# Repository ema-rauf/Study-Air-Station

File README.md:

# Study Air Station

A desk air quality monitor. It measures CO2, fine dust, temperature and humidity, shows a live score on a color display, runs a fan when the air gets bad, and sends a Telegram message when it is time to open a window. Everything is logged to a microSD card.

## Why I made it

When I study in a closed room, CO2 climbs past 1500 ppm within an hour and I get tired without knowing why. I wanted a device that shows the number, reacts on its own and keeps a record, so I can see how a room behaves over a day.

## How it works

An ESP32 reads two sensors:

- SCD40 over I2C for CO2, temperature and humidity
- PMS5003 over UART for PM1.0, PM2.5 and PM10

From these it computes a 0 to 100 score and a state (fine, stuffy, alert). The score drives an RGB LED and a bar on the 2.0 inch ST7789 display. The display has three pages, switched with the page button: live values, a 24 hour CO2 graph, and system info.

Layout preview of the three alert states, drawn by the firmware's display code with sample values.

- **Fan.** A 5 V fan is switched by an IRLZ44N. It turns on at 1000 ppm CO2 or 25 ug/m3 PM2.5 and off again 200 ppm and 10 ug/m3 lower, with a 60 second minimum run or rest time so it does not chatter. A long press on the page button forces it on, off or back to auto.
- **Alerts.** At 1500 ppm or 55 ug/m3 the LED blinks red, the buzzer beeps every 30 seconds and a Telegram message is sent immediately. The silence button mutes the buzzer for 10 minutes, then it re-arms by itself. A second message goes out when the air is back to normal.
- **Logging.** One CSV line per minute with a timestamp goes to the microSD card, one file per day. Time comes from NTP, so there is no RTC.
- **Dashboard.** A password protected web page on the local network shows live values, the 24 hour graph, fan and silence controls, the thresholds (editable, kept in flash) and a download link for today's log.

## Hardware

Two layer board, 100 x 80 mm. The ESP32 DevKit plugs into sockets. The SCD40, display, microSD module and PMS5003 connect with short jumper cables to pin headers, so each can sit where it works best in the case. The fan and the 5 V supply use screw terminals. The board takes 5 V on a screw terminal, through a Schottky diode against reverse polarity. Use the ESP32 USB port for programming with the 5 V terminal unplugged.

| Function | ESP32 pin |
| --- | --- |
| SCD40 SDA / SCL | IO21 / IO22 |
| PMS5003 TX to ESP32 / ESP32 to PMS5003 RX | IO16 / IO17 |
| TFT SCK, MOSI | IO33, IO25 (shared with the SD card) |
| TFT CS, DC, RES | IO14, IO27, IO26 |
| SD MISO, CS | IO34, IO32 |
| Fan gate | IO23 |
| Buzzer | IO4 |
| RGB LED R, G, B | IO19, IO18, IO5 |
| Silence button, page button | IO36, IO39 (10k pull-ups on the board) |

## Case

`cad/air_station_case.step` holds a base, a lid and two button caps. The PCB sits on four standoffs on the left. The bay on the right holds the PMS5003 on the floor, the microSD module and the SCD40 standing on their edges in rib slots, and a 25 mm fan on the back wall. The base has a USB opening, a cable opening for the 5 V input, intake slots, an SD card slot in the east wall and air slots for the SCD40. The lid has the display window above the bay and two button holes with printed caps. It takes about 120 g of filament.

## Firmware

`firmware/air_station/air_station.ino`, built with the Arduino IDE.

1. Install the ESP32 board package (board: ESP32 Dev Module).
2. Install the libraries Adafruit GFX Library and Adafruit ST7789 Library.
3. Edit the settings block at the top: WiFi name and password, dashboard password, Telegram bot token and chat id (optional), time zone.
4. Flash. The dashboard stays off until the default dashboard password is changed.

Buttons: silence short press mutes or unmutes. Page short press changes the page, long press cycles the fan mode.

Telegram alerts use HTTPS without certificate checking, so keep the bot token to a bot used only for this. The dashboard uses plain HTTP and basic authentication, so use it on a trusted network only.

## Files

- `hardware/` KiCad project (schematic, PCB, project libraries)
- `firmware/air_station/` Arduino sketch
- `cad/` case, STEP
- `BOM.csv` parts, prices, links
- `images/` renders

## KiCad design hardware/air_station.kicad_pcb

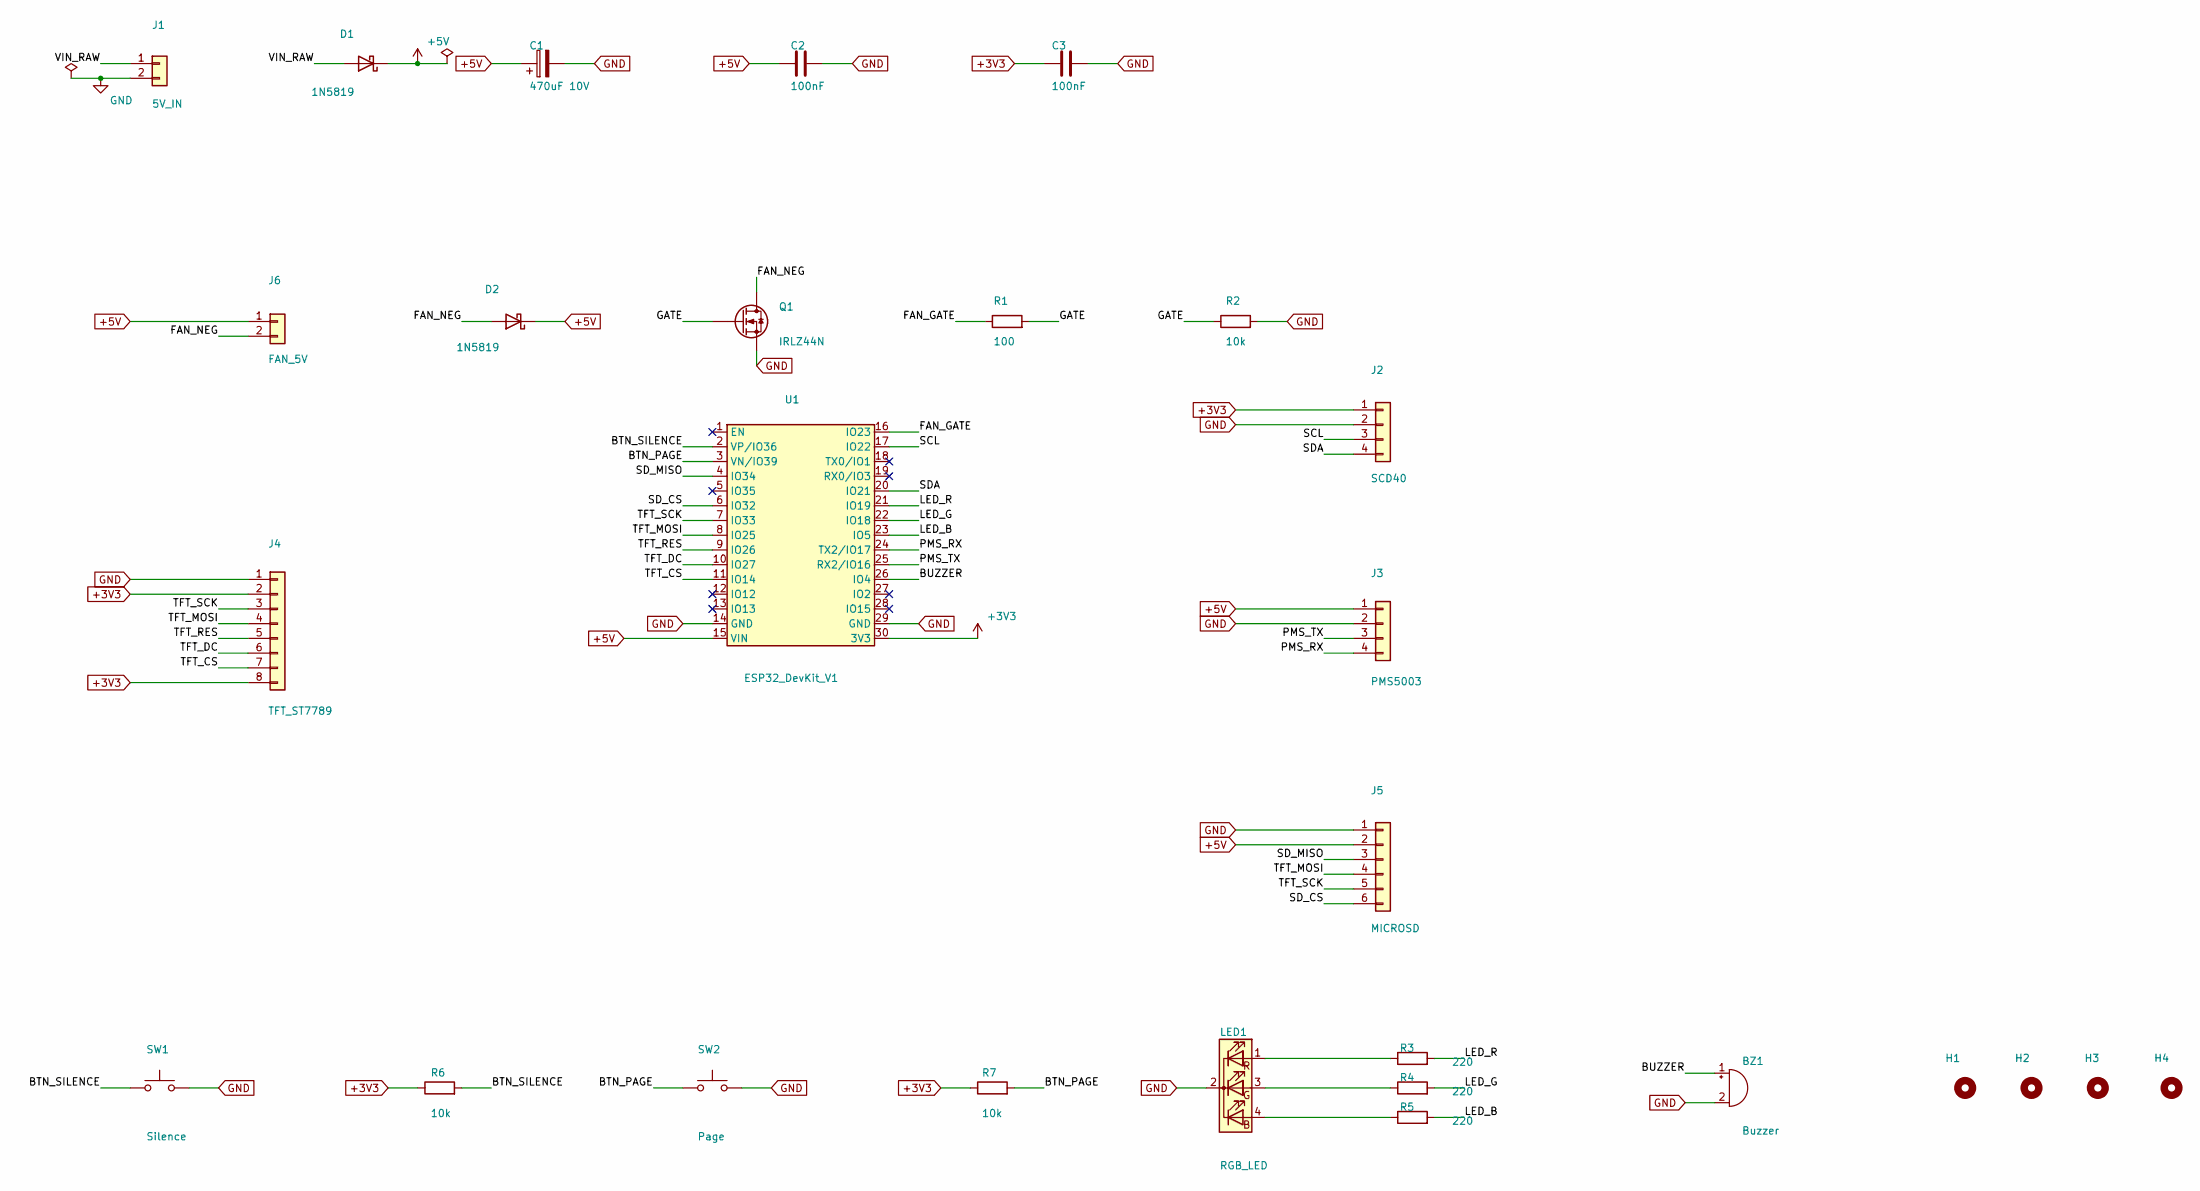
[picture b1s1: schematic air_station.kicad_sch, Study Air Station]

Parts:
BZ1: Buzzer; Buzzer_12x9.5RM7.6
C1: 470uF 10V; CP_Radial_D8.0mm_P3.50mm
C2, C3: 100nF; C_Disc_D5.0mm_W2.5mm_P5.00mm
D1, D2: 1N5819; D_DO-41_SOD81_P10.16mm_Horizontal
H1, H2, H3, H4: MountingHole_3.2mm; MountingHole_3.2mm_M3
J1: 5V_IN; TerminalBlock_Phoenix_MKDS-1,5-2-5.08_1x02_P5.08mm_Horizont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
J2: SCD40; PinHeader_1x04_P2.54mm_Vertical
J3: PMS5003; PinHeader_1x04_P2.54mm_Vertical
J4: TFT_ST7789; PinHeader_1x08_P2.54mm_Vertical
J5: MICROSD; PinHeader_1x06_P2.54mm_Vertical
J6: FAN_5V; TerminalBlock_Phoenix_MKDS-1,5-2-5.08_1x02_P5.08mm_Horizont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
LED1: RGB_LED; LED_D5.0mm-4_RGB_Wide
Q1: IRLZ44N; TO-220-3_Vertical
R1: 100; R_Axial_DIN0204_L3.6mm_D1.6mm_P5.08mm_Horizontal
R2, R6, R7: 10k; R_Axial_DIN0204_L3.6mm_D1.6mm_P5.08mm_Horizontal
R3, R4, R5: 220; R_Axial_DIN0204_L3.6mm_D1.6mm_P5.08mm_Horizontal
SW1: Silence; SW_Tactile_6mm_Diagonal
SW2: Page; SW_Tactile_6mm_Diagonal
U1: ESP32_DevKit_V1; ESP32_DevKit_V1_30pin_Socket

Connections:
+3V3: C3.1, J2.1, J4.2, J4.8, R6.1, R7.1, U1.30 (3V3)
+5V: C1.1, C2.1, D1.1 (K), D2.1 (K), J3.1, J5.2, J6.1, U1.15 (VIN)
/BTN_PAGE: R7.2, SW2.1, U1.3 (VN/IO39)
/BTN_SILENCE: R6.2, SW1.1, U1.2 (VP/IO36)
/BUZZER: BZ1.1 (+), U1.26 (IO4)
/FAN_GATE: R1.1, U1.16 (IO23)
/FAN_NEG: D2.2 (A), J6.2, Q1.2 (D)
/GATE: Q1.1 (G), R1.2, R2.1
/LED_B: R5.2, U1.23 (IO5)
/LED_G: R4.2, U1.22 (IO18)
/LED_R: R3.2, U1.21 (IO19)
/PMS_RX: J3.4, U1.24 (TX2/IO17)
/PMS_TX: J3.3, U1.25 (RX2/IO16)
/SCL: J2.3, U1.17 (IO22)
/SDA: J2.4, U1.20 (IO21)
/SD_CS: J5.6, U1.6 (IO32)
/SD_MISO: J5.3, U1.4 (IO34)
/TFT_CS: J4.7, U1.11 (IO14)
/TFT_DC: J4.6, U1.10 (IO27)
/TFT_MOSI: J4.4, J5.4, U1.8 (IO25)
/TFT_RES: J4.5, U1.9 (IO26)
/TFT_SCK: J4.3, J5.5, U1.7 (IO33)
/VIN_RAW: D1.2 (A), J1.1
GND: BZ1.2 (-), C1.2, C2.2, C3.2, J1.2, J2.2, J3.2, J4.1, J5.1, LED1.2 (K), Q1.3 (S), R2.2, SW1.2, SW2.2, U1.14 (GND), U1.29 (GND)
unnamed: LED1.4 (B), R5.1
unnamed: LED1.3 (G), R4.1
unnamed: LED1.1 (R), R3.1

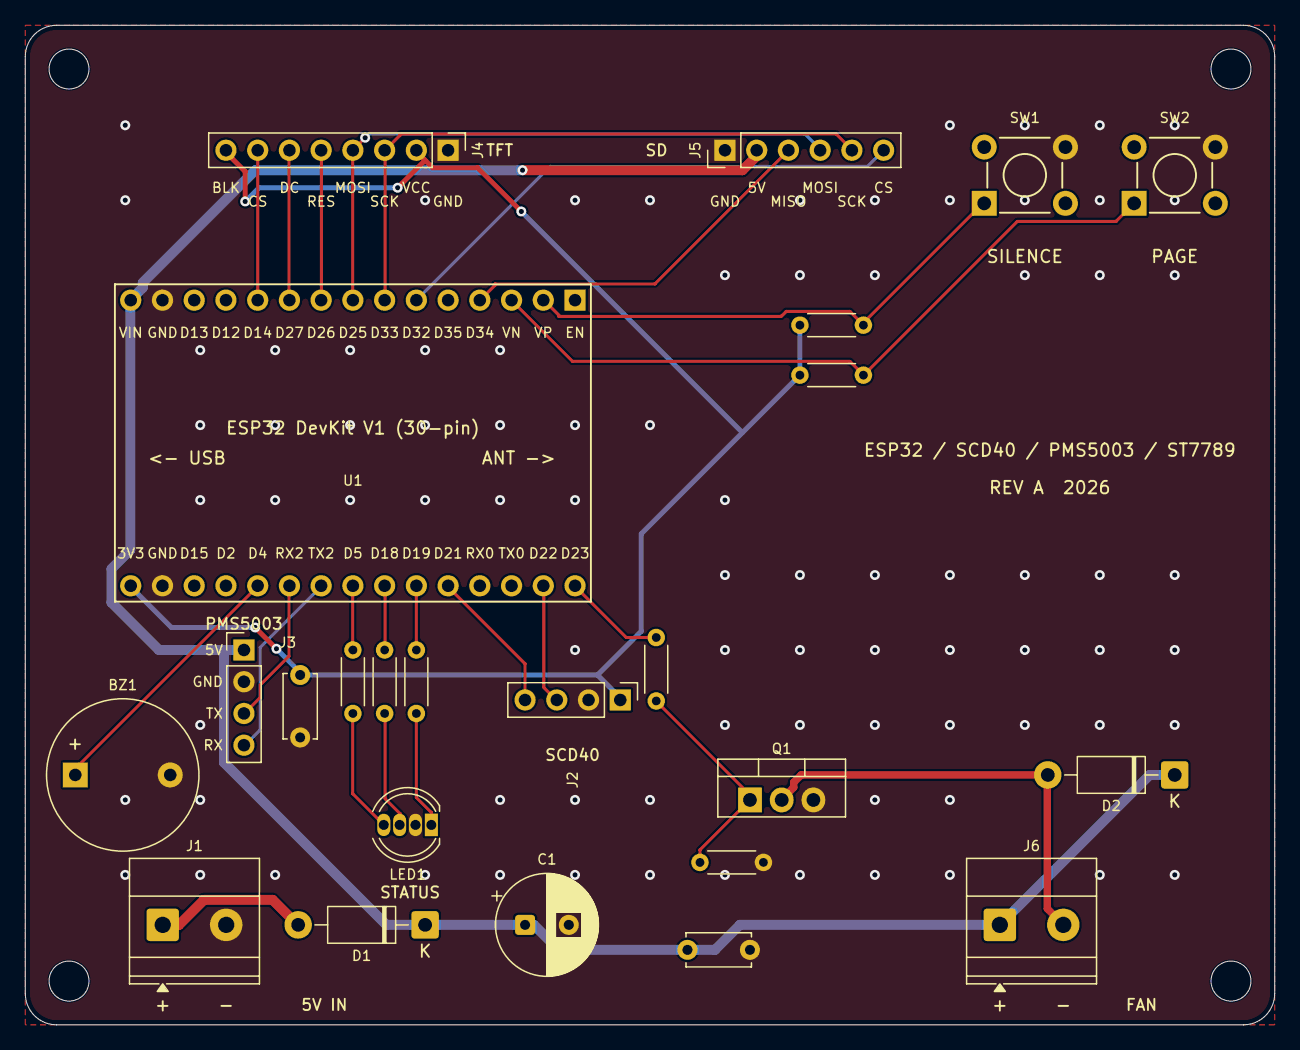
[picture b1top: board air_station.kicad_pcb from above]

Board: 2 copper layers, 100.0 x 80.0 mm, 28 parts (0 on the bottom side), 27 nets.

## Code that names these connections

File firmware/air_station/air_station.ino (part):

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
// ---------------------------------------------------------------- pins
const int PIN_SDA = 21, PIN_SCL = 22;
const int PIN_PMS_RX = 16;                 // ESP32 RX2, wired to PMS5003 TX
const int PIN_PMS_TX = 17;                 // ESP32 TX2, wired to PMS5003 RX
const int PIN_SCK = 33, PIN_MOSI = 25, PIN_MISO = 34;
const int PIN_TFT_CS = 14, PIN_TFT_DC = 27, PIN_TFT_RST = 26;
const int PIN_SD_CS = 32;
const int PIN_FAN = 23, PIN_BUZZER = 4;
const int PIN_LED_R = 19, PIN_LED_G = 18, PIN_LED_B = 5;
const int PIN_BTN_SILENCE = 36, PIN_BTN_PAGE = 39;

// ---------------------------------------------------------------- state
SPIClass spiBus(VSPI);
Adafruit_ST7789 tft(&spiBus, PIN_TFT_CS, PIN_TFT_DC, PIN_TFT_RST);
WebServer server(80);
Preferences prefs;

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  unsigned long since;
  Button(int p) : pin(p), down(false), longDone(false), since(0) {}
};
Button btnSilence(PIN_BTN_SILENCE), btnPage(PIN_BTN_PAGE);

bool fanOn = false;
unsigned long fanChangedAt = 0;
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}

void setLed(bool r, bool g, bool b) {
  digitalWrite(PIN_LED_R, r);
  digitalWrite(PIN_LED_G, g);
  digitalWrite(PIN_LED_B, b);
}

void updateLed() {
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  if (level != LV_ALERT) lastBeepAt = 0;
  if (beepsLeft > 0 && now >= beepToggleAt) {
    beepState = !beepState;
    digitalWrite(PIN_BUZZER, beepState);
    beepsLeft--;
    beepToggleAt = now + 150;
  }
  if (beepsLeft == 0 && beepState) { beepState = false; digitalWrite(PIN_BUZZER, LOW); }
}

void setSilence(bool on) {
  silenced = on;
  silencedAt = millis();
  if (on) { beepsLeft = 0; digitalWrite(PIN_BUZZER, LOW); beepState = false; }
  toast = on ? "Silenced for 10 min" : "Silence cancelled";
  toastUntil = millis() + 3000;
}
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}

void sdMount() {
  sdOk = SD.begin(PIN_SD_CS, spiBus, 4000000);
}

void logTick() {
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void setup() {
  Serial.begin(115200);
  pinMode(PIN_FAN, OUTPUT);     digitalWrite(PIN_FAN, LOW);
  pinMode(PIN_BUZZER, OUTPUT);  digitalWrite(PIN_BUZZER, LOW);
  pinMode(PIN_LED_R, OUTPUT);
  pinMode(PIN_LED_G, OUTPUT);
  pinMode(PIN_LED_B, OUTPUT);
  pinMode(PIN_BTN_SILENCE, INPUT);        // external pull-ups on the board
  pinMode(PIN_BTN_PAGE, INPUT);
  setLed(0, 0, 1);
  loadConfig();

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  Wire.begin(PIN_SDA, PIN_SCL);
  Wire.setClock(100000);
  scdBegin();
  Serial2.begin(9600, SERIAL_8N1, PIN_PMS_RX, PIN_PMS_TX);
  sdMount();

  WiFi.mode(WIFI_STA);
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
